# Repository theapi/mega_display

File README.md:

# mega_display
large 7 segment display inspired by Fran Blanche https://www.youtube.com/watch?v=M3jyMX8EXAQ

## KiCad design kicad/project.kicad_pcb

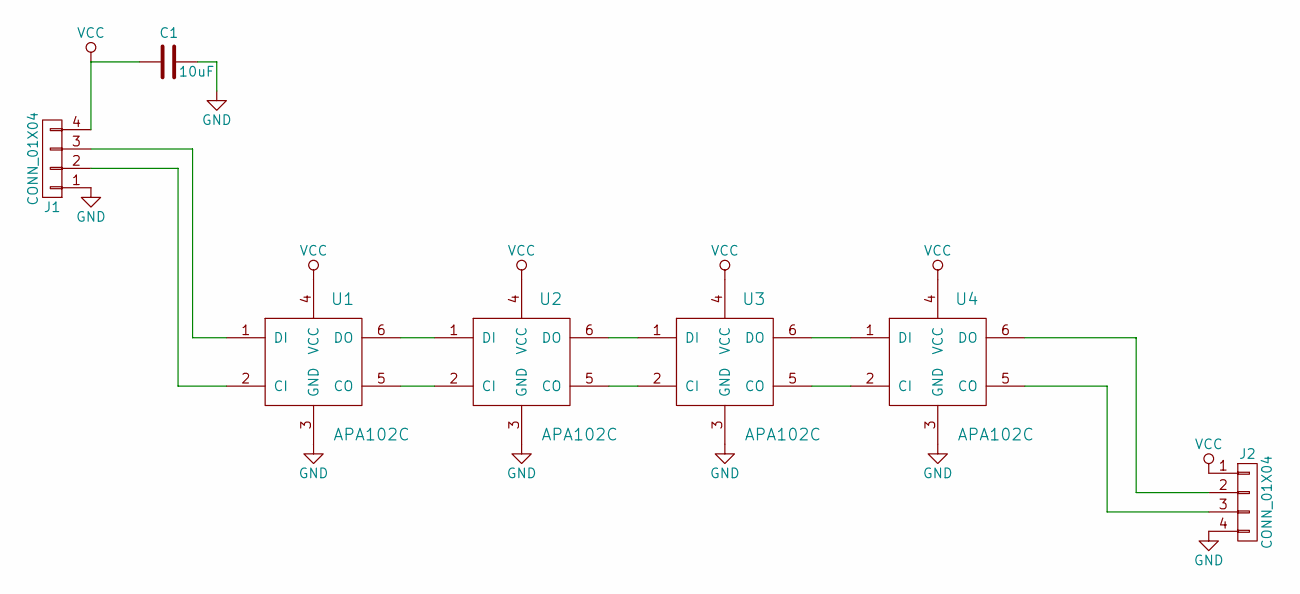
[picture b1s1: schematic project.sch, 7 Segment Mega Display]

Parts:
C1: 10uF; C_0805_HandSoldering
J1, J2: CONN_01X04; Pin_Header_Straight_1x04_Pitch2.54mm
U1, U2, U3, U4: APA102C; LED_WS2812-PLCC6

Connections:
GND: C1.1, J1.1, J2.4, U1.3 (GND), U2.3 (GND), U3.3 (GND), U4.3 (GND)
unnamed: J1.2, U1.2 (CI)
unnamed: J1.3, U1.1 (DI)
unnamed: J2.2, U4.6 (DO)
unnamed: J2.3, U4.5 (CO)
unnamed: U1.5 (CO), U2.2 (CI)
unnamed: U1.6 (DO), U2.1 (DI)
unnamed: U2.5 (CO), U3.2 (CI)
unnamed: U2.6 (DO), U3.1 (DI)
unnamed: U3.5 (CO), U4.2 (CI)
unnamed: U3.6 (DO), U4.1 (DI)
VCC: C1.2, J1.4, J2.1, U1.4 (VCC), U2.4 (VCC), U3.4 (VCC), U4.4 (VCC)

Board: 2 copper layers, 7 parts (0 on the bottom side), 12 nets, no tracks yet.

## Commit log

2018-03-28 Blank Kicad project & LED driver datasheet
2018-03-28 Removed unused libs
2018-03-31 7-segment.svg
2018-04-01 130mm wide
2018-04-17 APA102C for the leds
2018-04-19 4 leds only
2018-04-19 Inital footprints import
